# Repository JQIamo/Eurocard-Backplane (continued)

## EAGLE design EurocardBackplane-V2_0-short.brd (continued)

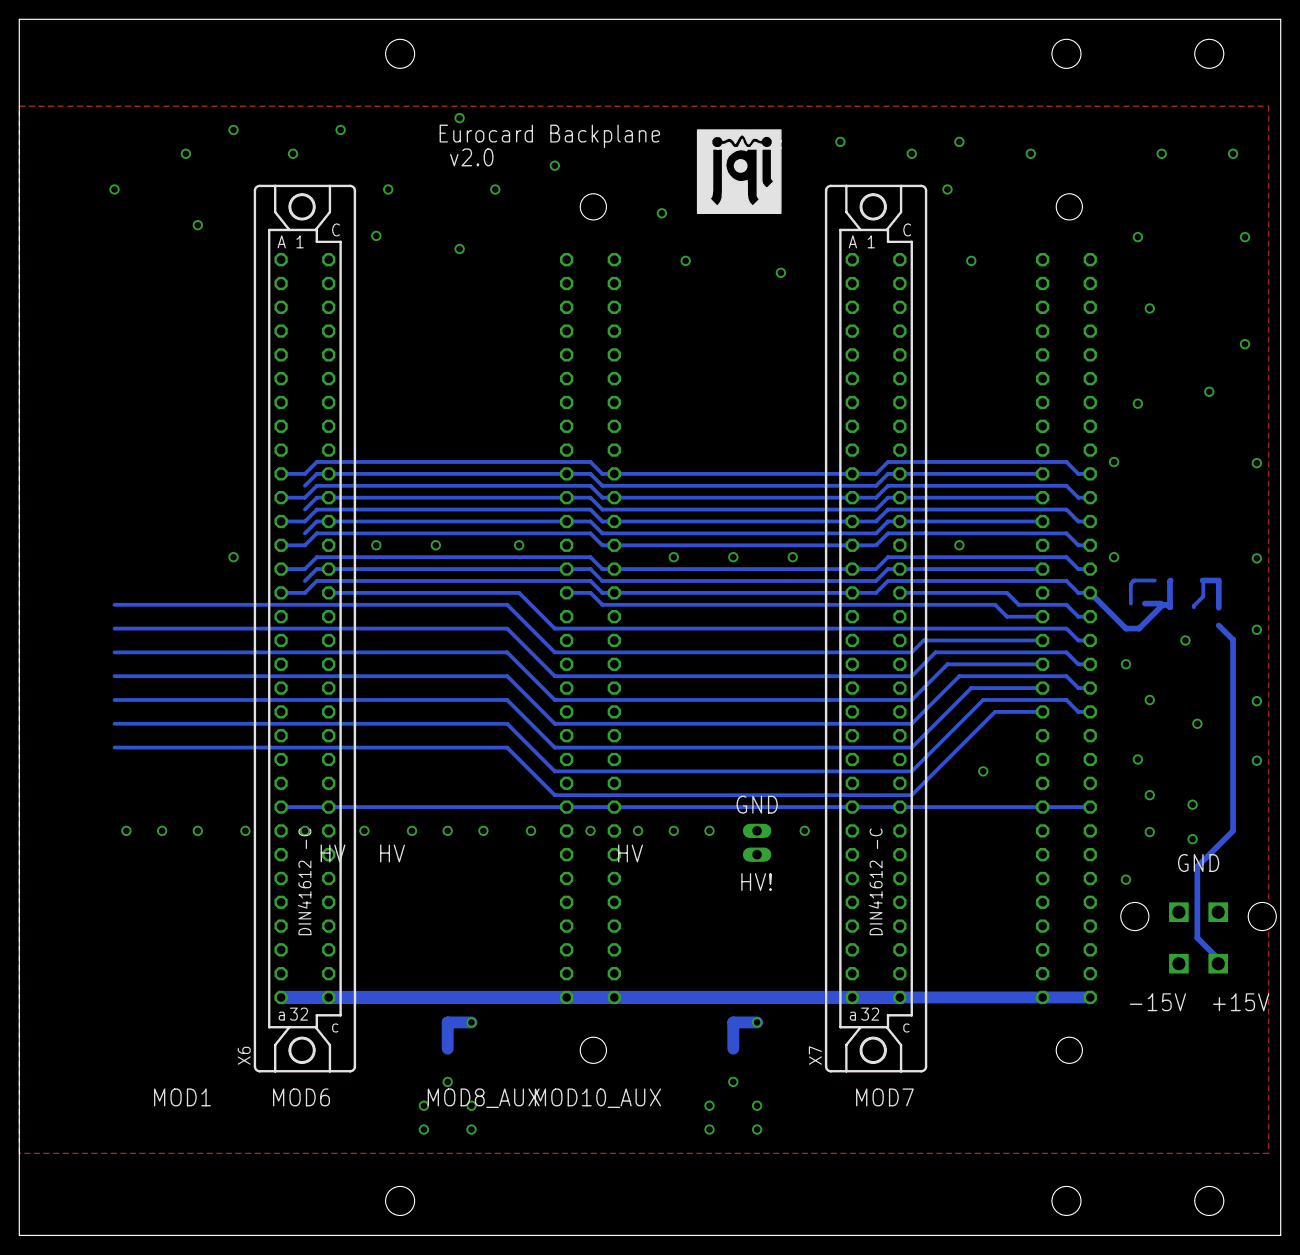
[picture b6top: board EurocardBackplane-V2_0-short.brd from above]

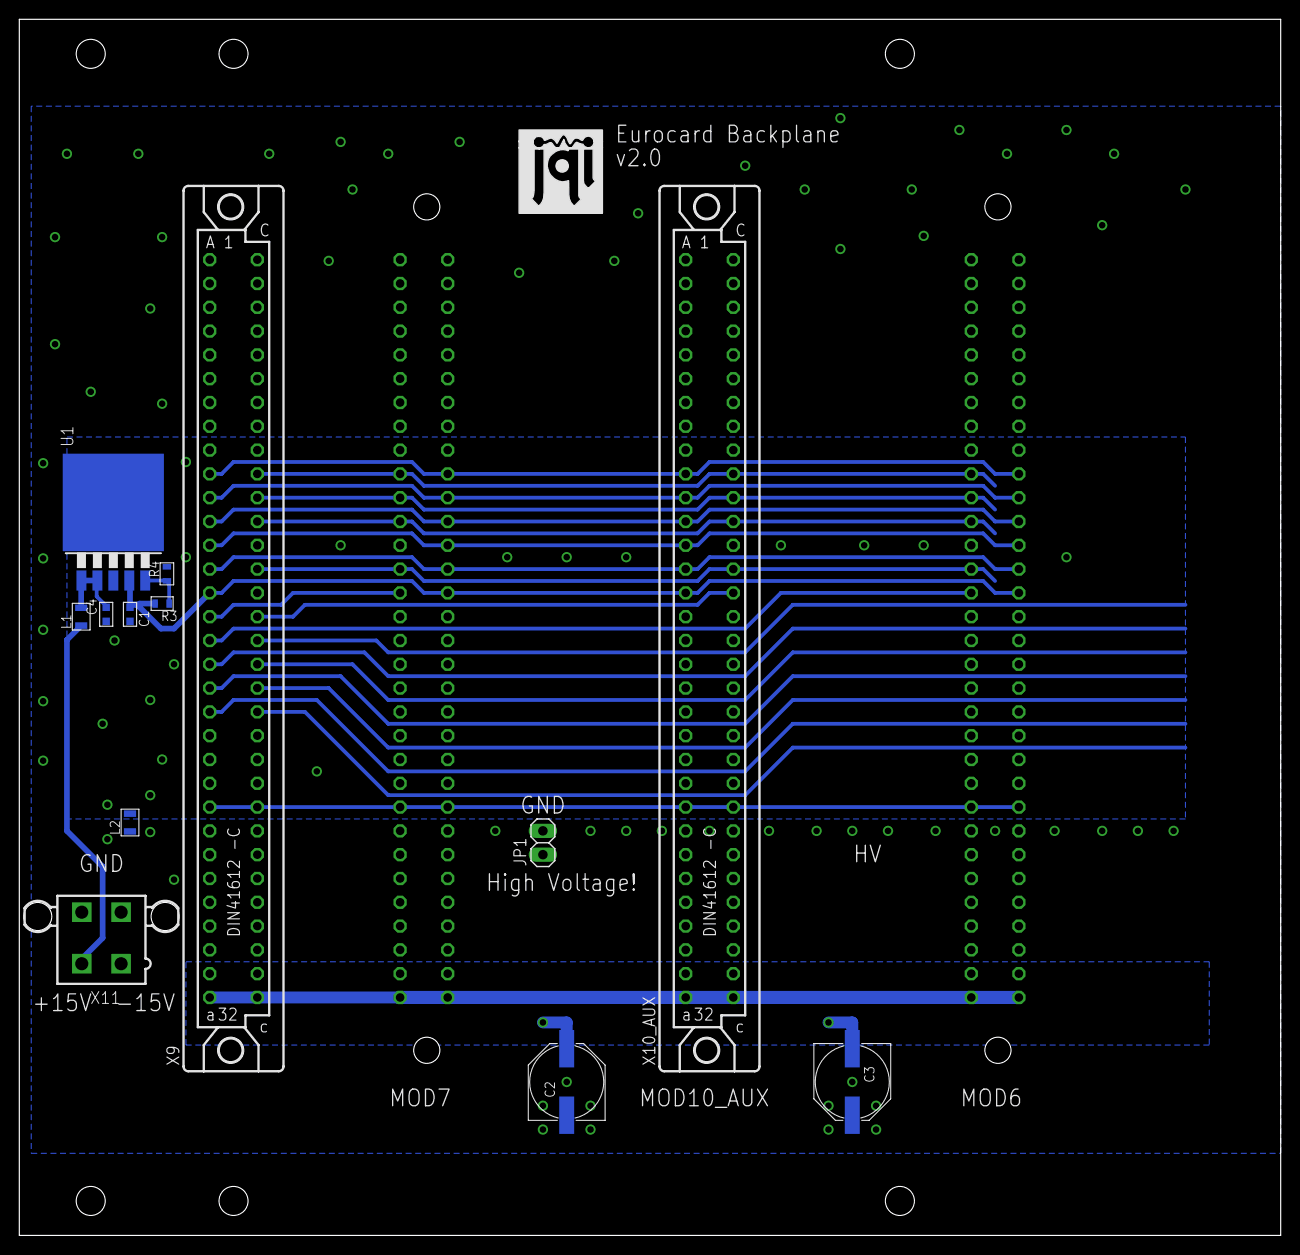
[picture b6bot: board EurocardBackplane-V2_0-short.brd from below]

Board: 4 copper layers, 134.6 x 129.8 mm, 18 parts (14 on the bottom side), 60 nets.

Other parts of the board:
U$1, U$4: JQI_LOGO_NEGATIVE-SILKSCREEN
U$2: BACKPLN-PROTO

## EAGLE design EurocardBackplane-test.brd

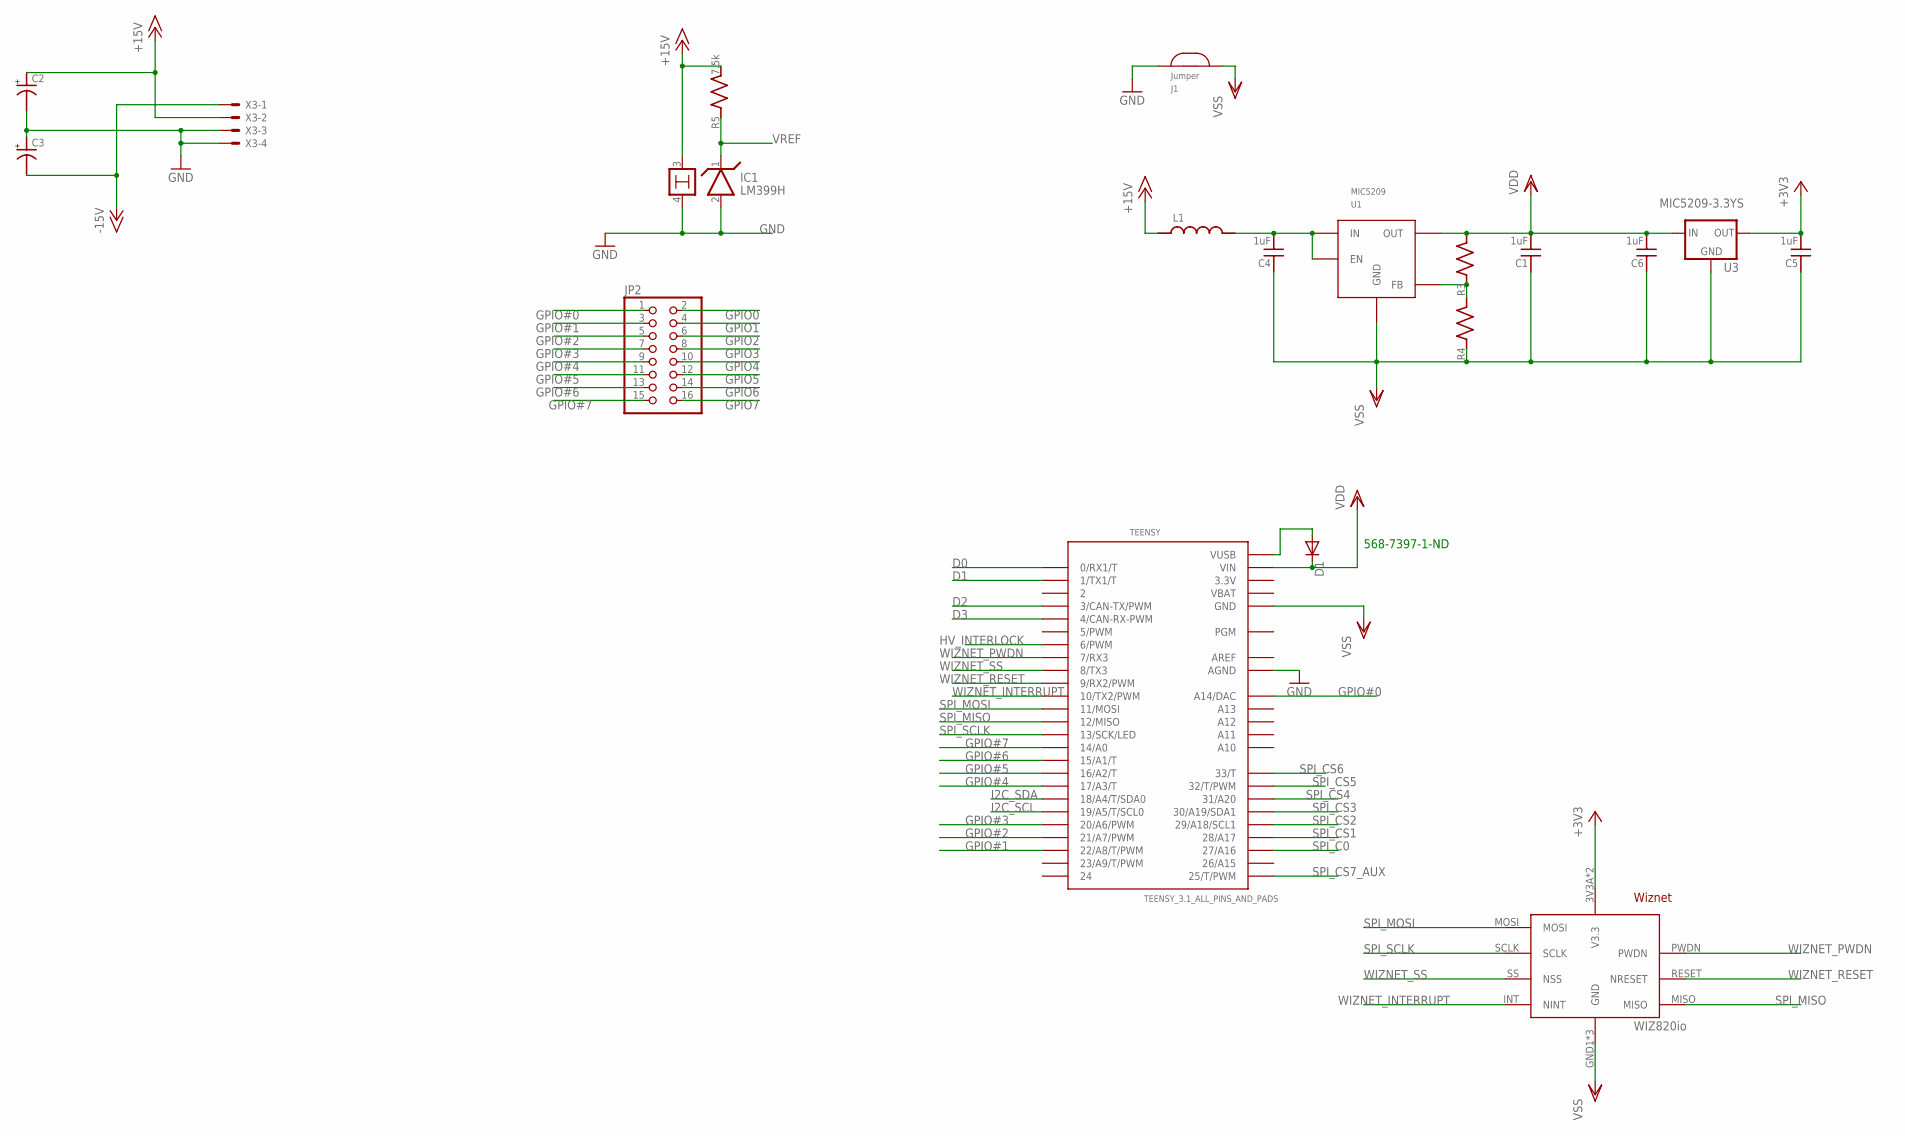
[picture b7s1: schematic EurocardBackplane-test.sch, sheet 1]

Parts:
C1, C4, C5, C6: 1uF; C_MLCC_0603
C2, C3: C_POL_SMDF; PANASONIC_F
D1: DIODE-SOD523; SOD523
IC1: LM399H; TO39/4
J1: JUMPER; JUMP
JP2: PINHD-2X8; 2X08
L1: L_FERRITE_SMDLFERRITE_0805; R_0805
R3, R4: R_SMDR0603; R_0603
R5: 7.5k; R_0603
TEENSY: TEENSY_3.1_ALL_PINS_AND_PADS; TEENSY_3.1_ALLPINS
U1: MIC5209; TO263-5
U2: WIZ820IO; WIZNET
U3: MIC5209-3.3YS; SOT223-S
X3: 5566-4

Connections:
3.3V: TEENSY.3.3V, TEENSY.3.3V1 (3.3V), TEENSY.3.3V2 (3.3V)
+3V3: C5.P$2 (2), U2.3V3A (V3.3), U2.3V3B (V3.3), U3.3 (OUT)
+15V: C2.+, IC1.3, L1.P$1 (1), R5.P$2 (2), X3.2; also elsewhere on the board
-15V: C3.-, X3.1; also elsewhere on the board
AREF: TEENSY.AREF
D0: TEENSY.0 (0/RX1/T); also elsewhere on the board
D1: TEENSY.1 (1/TX1/T); also elsewhere on the board
D2: TEENSY.3 (3/CAN-TX/PWM); also elsewhere on the board
D3: TEENSY.4 (4/CAN-RX-PWM); also elsewhere on the board
GND: C2.-, C3.+, IC1.2, IC1.4, J1.P$2, TEENSY.AGND, X3.3, X3.4; also elsewhere on the board
GPIO0: JP2.2; also elsewhere on the board
GPIO1: JP2.4; also elsewhere on the board
GPIO2: JP2.6; also elsewhere on the board
GPIO3: JP2.8; also elsewhere on the board
GPIO4: JP2.10; also elsewhere on the board
GPIO5: JP2.12; also elsewhere on the board
GPIO6: JP2.14; also elsewhere on the board
GPIO7: JP2.16; also elsewhere on the board
GPIO#0: JP2.1, TEENSY.A14 (A14/DAC)
GPIO#1: JP2.3, TEENSY.22/A8 (22/A8/T/PWM)
GPIO#2: JP2.5, TEENSY.21/A7 (21/A7/PWM)
GPIO#3: JP2.7, TEENSY.20/A6 (20/A6/PWM)
GPIO#4: JP2.9, TEENSY.17/A3 (17/A3/T)
GPIO#5: JP2.11, TEENSY.16/A2 (16/A2/T)
GPIO#6: JP2.13, TEENSY.15/A1 (15/A1/T)
GPIO#7: JP2.15, TEENSY.14/A0
HV_INTERLOCK: TEENSY.6 (6/PWM); also elsewhere on the board
I2C_SCL: TEENSY.19/A5 (19/A5/T/SCL0); also elsewhere on the board
I2C_SDA: TEENSY.18/A4 (18/A4/T/SDA0); also elsewhere on the board
unnamed: C4.P$2 (2), L1.P$2 (2), U1.1 (EN), U1.2 (IN)
unnamed: D1.A, TEENSY.VUSB
unnamed: R3.P$1 (1), R4.P$2 (2), U1.5 (FB)
SPI_C0: TEENSY.27 (27/A16)
SPI_CS1: TEENSY.28 (28/A17)
SPI_CS2: TEENSY.29 (29/A18/SCL1)
SPI_CS3: TEENSY.30 (30/A19/SDA1)
SPI_CS4: TEENSY.31 (31/A20)
SPI_CS5: TEENSY.32 (32/T/PWM); also elsewhere on the board
SPI_CS6: TEENSY.33 (33/T); also elsewhere on the board
SPI_CS7_AUX: TEENSY.25 (25/T/PWM); also elsewhere on the board
SPI_MISO: TEENSY.12 (12/MISO), U2.MISO; also elsewhere on the board
SPI_MOSI: TEENSY.11 (11/MOSI), U2.MOSI; also elsewhere on the board
SPI_SCLK: TEENSY.13 (13/SCK/LED), U2.SCLK; also elsewhere on the board
VBAT: TEENSY.VBAT
VDD: C1.P$2 (2), C6.P$2 (2), D1.C, R3.P$2 (2), TEENSY.VIN, U1.4 (OUT), U3.1 (IN)
VREF: IC1.1, R5.P$1 (1); also elsewhere on the board
VSS: C1.P$1 (1), C4.P$1 (1), C5.P$1 (1), C6.P$1 (1), J1.P$1, R4.P$1 (1), TEENSY.GND, TEENSY.GND1 (GND), TEENSY.GND2 (GND), U1.3 (GND), U1.6 (GND), U2.GND1 (GND), U2.GND2 (GND), U2.GND3 (GND), U3.2 (GND), U3.4 (GND)
WIZNET_INTERRUPT: TEENSY.10 (10/TX2/PWM), U2.INT (NINT)
WIZNET_PWDN: TEENSY.7 (7/RX3), U2.PWDN
WIZNET_RESET: TEENSY.9 (9/RX2/PWM), U2.RESET (NRESET)
WIZNET_SS: TEENSY.8 (8/TX3), U2.SS (NSS)

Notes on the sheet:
568-7397-1-ND

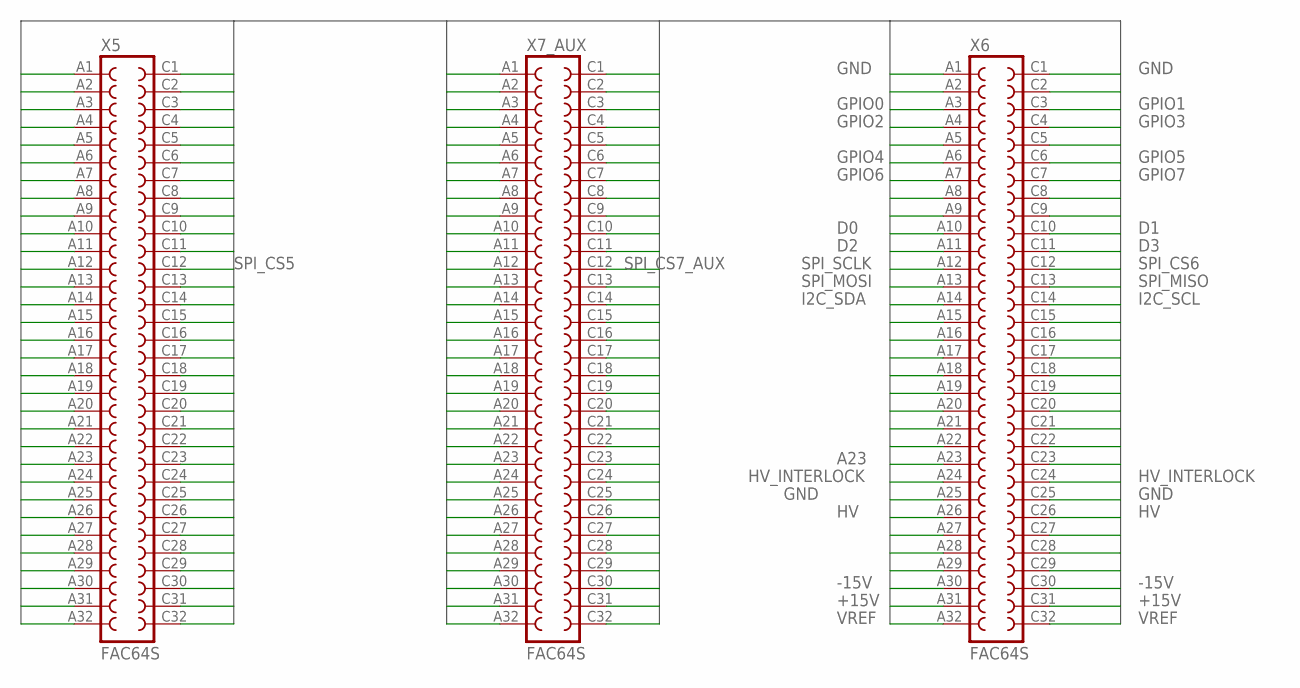
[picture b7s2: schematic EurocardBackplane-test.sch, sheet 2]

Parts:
X5, X6, X7_AUX: FAC64S

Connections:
+15V: X5.A31, X5.C31, X6.A31, X6.C31, X7_AUX.A31, X7_AUX.C31; also elsewhere on the board
-15V: X5.A30, X5.C30, X6.A30, X6.C30, X7_AUX.A30, X7_AUX.C30; also elsewhere on the board
A2: X5.A2, X6.A2, X7_AUX.A2
A5: X5.A5, X6.A5, X7_AUX.A5
A8: X5.A8, X6.A8, X7_AUX.A8
A9: X5.A9, X6.A9, X7_AUX.A9
A15: X5.A15, X6.A15, X7_AUX.A15
A16: X5.A16, X6.A16, X7_AUX.A16
A17: X5.A17, X6.A17, X7_AUX.A17
A18: X5.A18, X6.A18, X7_AUX.A18
A19: X5.A19, X6.A19, X7_AUX.A19
A20: X5.A20, X6.A20, X7_AUX.A20
A21: X5.A21, X6.A21, X7_AUX.A21
A22: X5.A22, X6.A22, X7_AUX.A22
A23: X5.A23, X6.A23, X7_AUX.A23
A27: X5.A27, X6.A27, X7_AUX.A27
A28: X5.A28, X6.A28, X7_AUX.A28
A29: X5.A29, X6.A29, X7_AUX.A29
C2: X5.C2, X6.C2, X7_AUX.C2
C5: X5.C5, X6.C5, X7_AUX.C5
C8: X5.C8, X6.C8, X7_AUX.C8
C9: X5.C9, X6.C9, X7_AUX.C9
C15: X5.C15, X6.C15, X7_AUX.C15
C16: X5.C16, X6.C16, X7_AUX.C16
C17: X5.C17, X6.C17, X7_AUX.C17
C18: X5.C18, X6.C18, X7_AUX.C18
C19: X5.C19, X6.C19, X7_AUX.C19
C20: X5.C20, X6.C20, X7_AUX.C20
C21: X5.C21, X6.C21, X7_AUX.C21
C22: X5.C22, X6.C22, X7_AUX.C22
C23: X5.C23, X6.C23, X7_AUX.C23
C27: X5.C27, X6.C27, X7_AUX.C27
C28: X5.C28, X6.C28, X7_AUX.C28
C29: X5.C29, X6.C29, X7_AUX.C29
D0: X5.A10, X6.A10, X7_AUX.A10; also elsewhere on the board
D1: X5.C10, X6.C10, X7_AUX.C10; also elsewhere on the board
D2: X5.A11, X6.A11, X7_AUX.A11; also elsewhere on the board
D3: X5.C11, X6.C11, X7_AUX.C11; also elsewhere on the board
GND: X5.A1, X5.A25, X5.C1, X5.C25, X6.A1, X6.A25, X6.C1, X6.C25, X7_AUX.A1, X7_AUX.A25, X7_AUX.C1, X7_AUX.C25; also elsewhere on the board
GPIO0: X5.A3, X6.A3, X7_AUX.A3; also elsewhere on the board
GPIO1: X5.C3, X6.C3, X7_AUX.C3; also elsewhere on the board
GPIO2: X5.A4, X6.A4, X7_AUX.A4; also elsewhere on the board
GPIO3: X5.C4, X6.C4, X7_AUX.C4; also elsewhere on the board
GPIO4: X5.A6, X6.A6, X7_AUX.A6; also elsewhere on the board
GPIO5: X5.C6, X6.C6, X7_AUX.C6; also elsewhere on the board
GPIO6: X5.A7, X6.A7, X7_AUX.A7; also elsewhere on the board
GPIO7: X5.C7, X6.C7, X7_AUX.C7; also elsewhere on the board
HV: X5.A26, X5.C26, X6.A26, X6.C26, X7_AUX.A26, X7_AUX.C26
HV_INTERLOCK: X5.A24, X5.C24, X6.A24, X6.C24, X7_AUX.A24, X7_AUX.C24; also elsewhere on the board
I2C_SCL: X5.C14, X6.C14, X7_AUX.C14; also elsewhere on the board
I2C_SDA: X5.A14, X6.A14, X7_AUX.A14; also elsewhere on the board
SPI_CS5: X5.C12; also elsewhere on the board
SPI_CS6: X6.C12; also elsewhere on the board
SPI_CS7_AUX: X7_AUX.C12; also elsewhere on the board
SPI_MISO: X5.C13, X6.C13, X7_AUX.C13; also elsewhere on the board
SPI_MOSI: X5.A13, X6.A13, X7_AUX.A13; also elsewhere on the board
SPI_SCLK: X5.A12, X6.A12, X7_AUX.A12; also elsewhere on the board
VREF: X5.A32, X5.C32, X6.A32, X6.C32, X7_AUX.A32, X7_AUX.C32; also elsewhere on the board

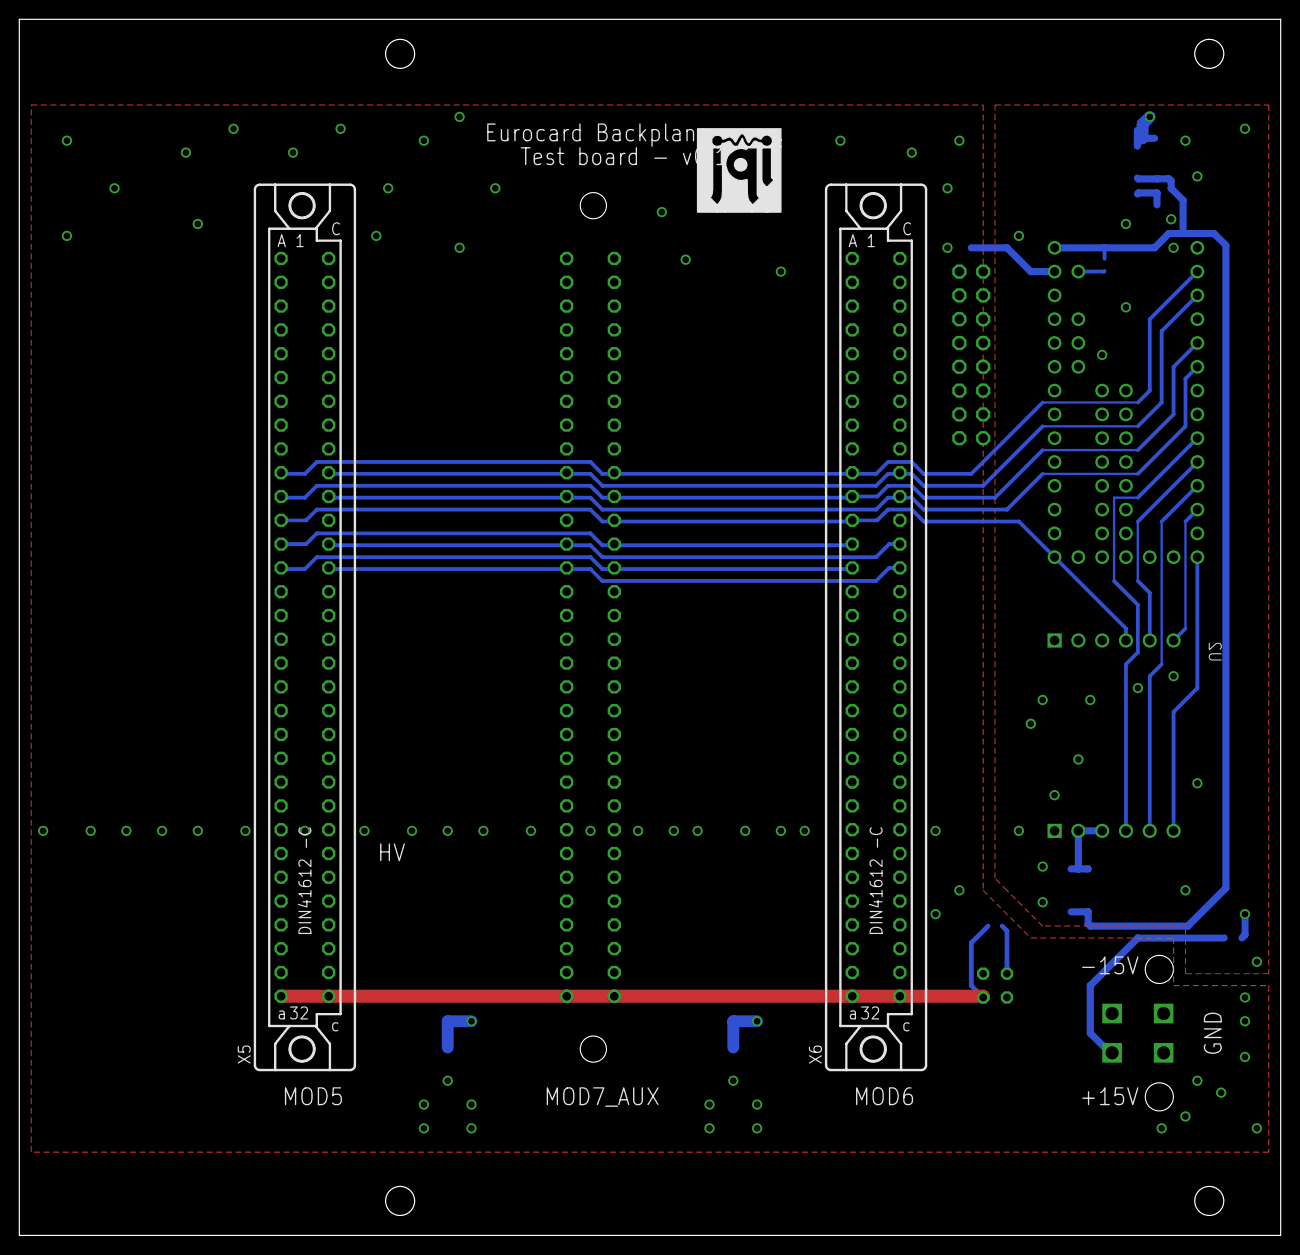
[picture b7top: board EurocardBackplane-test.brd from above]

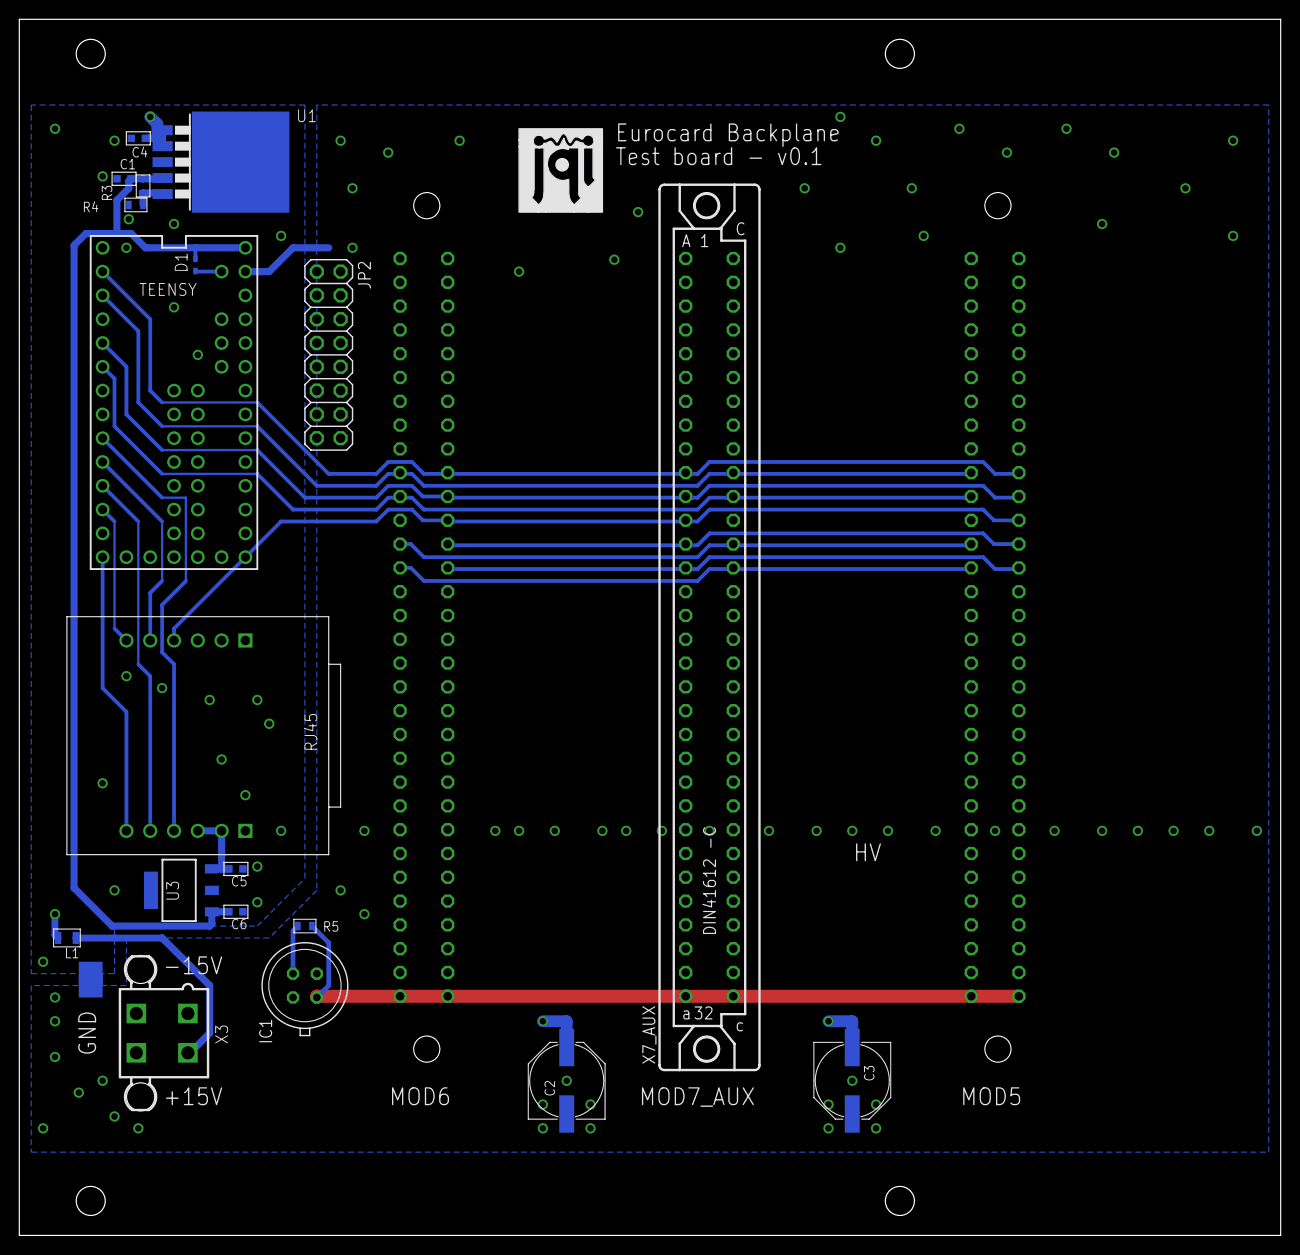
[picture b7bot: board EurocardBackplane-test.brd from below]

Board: 4 copper layers, 134.6 x 129.8 mm, 25 parts (21 on the bottom side), 77 nets.

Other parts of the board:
U$1, U$4: JQI_LOGO_NEGATIVE-SILKSCREEN
U$3: BACKPLN-PROTO

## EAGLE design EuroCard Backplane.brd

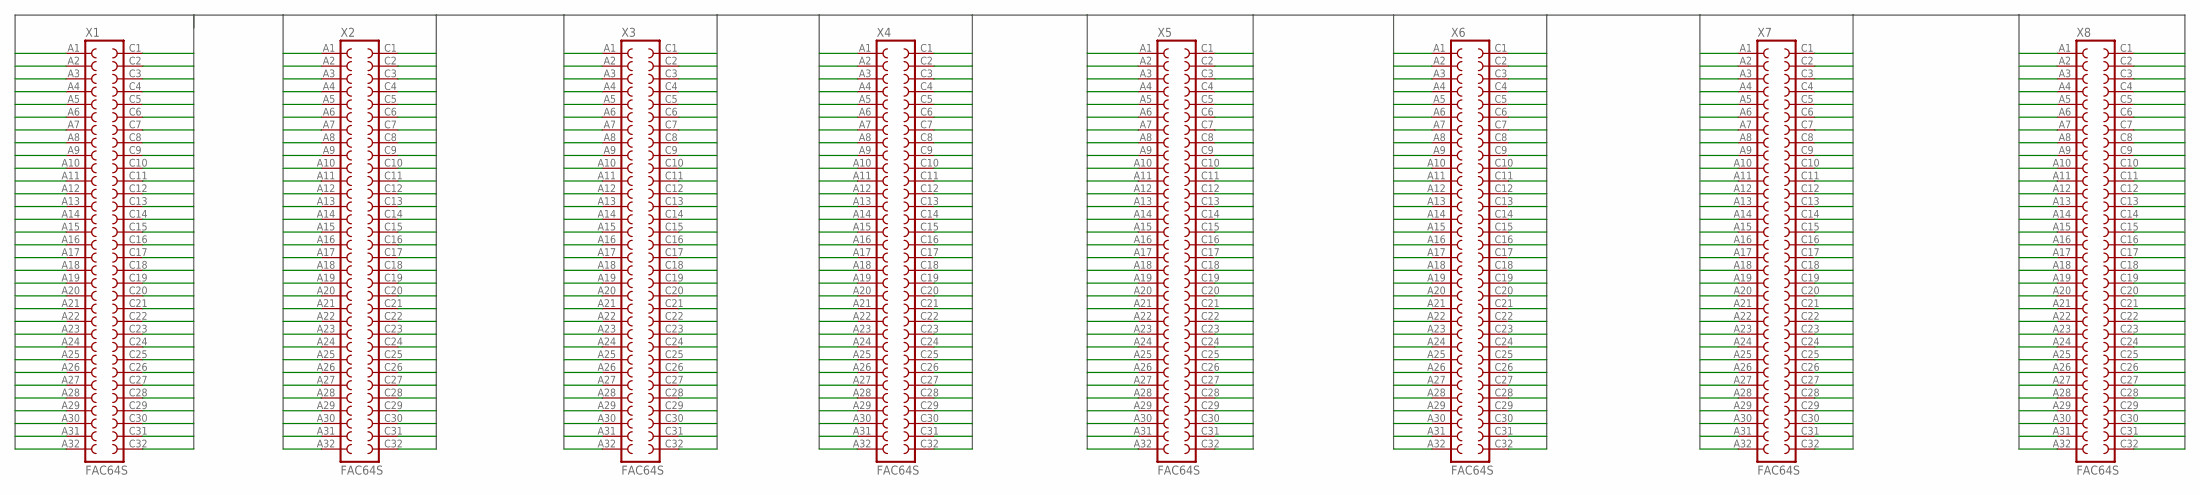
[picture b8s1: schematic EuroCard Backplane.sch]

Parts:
X1, X2, X3, X4, X5, X6, X7, X8: FAC64S

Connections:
A1: X1.A1, X2.A1, X3.A1, X4.A1, X5.A1, X6.A1, X7.A1, X8.A1
A2: X1.A2, X2.A2, X3.A2, X4.A2, X5.A2, X6.A2, X7.A2, X8.A2
A3: X1.A3, X2.A3, X3.A3, X4.A3, X5.A3, X6.A3, X7.A3, X8.A3
A4: X1.A4, X2.A4, X3.A4, X4.A4, X5.A4, X6.A4, X7.A4, X8.A4
A5: X1.A5, X2.A5, X3.A5, X4.A5, X5.A5, X6.A5, X7.A5, X8.A5
A6: X1.A6, X2.A6, X3.A6, X4.A6, X5.A6, X6.A6, X7.A6, X8.A6
A7: X1.A7, X2.A7, X3.A7, X4.A7, X5.A7, X6.A7, X7.A7, X8.A7
A8: X1.A8, X2.A8, X3.A8, X4.A8, X5.A8, X6.A8, X7.A8, X8.A8
A9: X1.A9, X2.A9, X3.A9, X4.A9, X5.A9, X6.A9, X7.A9, X8.A9
A10: X1.A10, X2.A10, X3.A10, X4.A10, X5.A10, X6.A10, X7.A10, X8.A10
A11: X1.A11, X2.A11, X3.A11, X4.A11, X5.A11, X6.A11, X7.A11, X8.A11
A12: X1.A12, X2.A12, X3.A12, X4.A12, X5.A12, X6.A12, X7.A12, X8.A12
A13: X1.A13, X2.A13, X3.A13, X4.A13, X5.A13, X6.A13, X7.A13, X8.A13
A14: X1.A14, X2.A14, X3.A14, X4.A14, X5.A14, X6.A14, X7.A14, X8.A14
A15: X1.A15, X2.A15, X3.A15, X4.A15, X5.A15, X6.A15, X7.A15, X8.A15
A16: X1.A16, X2.A16, X3.A16, X4.A16, X5.A16, X6.A16, X7.A16, X8.A16
A17: X1.A17, X2.A17, X3.A17, X4.A17, X5.A17, X6.A17, X7.A17, X8.A17
A18: X1.A18, X2.A18, X3.A18, X4.A18, X5.A18, X6.A18, X7.A18, X8.A18
A19: X1.A19, X2.A19, X3.A19, X4.A19, X5.A19, X6.A19, X7.A19, X8.A19
A20: X1.A20, X2.A20, X3.A20, X4.A20, X5.A20, X6.A20, X7.A20, X8.A20
A21: X1.A21, X2.A21, X3.A21, X4.A21, X5.A21, X6.A21, X7.A21, X8.A21
A22: X1.A22, X2.A22, X3.A22, X4.A22, X5.A22, X6.A22, X7.A22, X8.A22
A23: X1.A23, X2.A23, X3.A23, X4.A23, X5.A23, X6.A23, X7.A23, X8.A23
A24: X1.A24, X2.A24, X3.A24, X4.A24, X5.A24, X6.A24, X7.A24, X8.A24
A25: X1.A25, X2.A25, X3.A25, X4.A25, X5.A25, X6.A25, X7.A25, X8.A25
A26: X1.A26, X2.A26, X3.A26, X4.A26, X5.A26, X6.A26, X7.A26, X8.A26
A27: X1.A27, X2.A27, X3.A27, X4.A27, X5.A27, X6.A27, X7.A27, X8.A27
A28: X1.A28, X2.A28, X3.A28, X4.A28, X5.A28, X6.A28, X7.A28, X8.A28
A29: X1.A29, X2.A29, X3.A29, X4.A29, X5.A29, X6.A29, X7.A29, X8.A29
A30: X1.A30, X2.A30, X3.A30, X4.A30, X5.A30, X6.A30, X7.A30, X8.A30
A31: X1.A31, X2.A31, X3.A31, X4.A31, X5.A31, X6.A31, X7.A31, X8.A31
A32: X1.A32, X2.A32, X3.A32, X4.A32, X5.A32, X6.A32, X7.A32, X8.A32
C1: X1.C1, X2.C1, X3.C1, X4.C1, X5.C1, X6.C1, X7.C1, X8.C1
C2: X1.C2, X2.C2, X3.C2, X4.C2, X5.C2, X6.C2, X7.C2, X8.C2
C3: X1.C3, X2.C3, X3.C3, X4.C3, X5.C3, X6.C3, X7.C3, X8.C3
C4: X1.C4, X2.C4, X3.C4, X4.C4, X5.C4, X6.C4, X7.C4, X8.C4
C5: X1.C5, X2.C5, X3.C5, X4.C5, X5.C5, X6.C5, X7.C5, X8.C5
C6: X1.C6, X2.C6, X3.C6, X4.C6, X5.C6, X6.C6, X7.C6, X8.C6
C7: X1.C7, X2.C7, X3.C7, X4.C7, X5.C7, X6.C7, X7.C7, X8.C7
C8: X1.C8, X2.C8, X3.C8, X4.C8, X5.C8, X6.C8, X7.C8, X8.C8
C9: X1.C9, X2.C9, X3.C9, X4.C9, X5.C9, X6.C9, X7.C9, X8.C9
C10: X1.C10, X2.C10, X3.C10, X4.C10, X5.C10, X6.C10, X7.C10, X8.C10
C11: X1.C11, X2.C11, X3.C11, X4.C11, X5.C11, X6.C11, X7.C11, X8.C11
C12: X1.C12, X2.C12, X3.C12, X4.C12, X5.C12, X6.C12, X7.C12, X8.C12
C13: X1.C13, X2.C13, X3.C13, X4.C13, X5.C13, X6.C13, X7.C13, X8.C13
C14: X1.C14, X2.C14, X3.C14, X4.C14, X5.C14, X6.C14, X7.C14, X8.C14
C15: X1.C15, X2.C15, X3.C15, X4.C15, X5.C15, X6.C15, X7.C15, X8.C15
C16: X1.C16, X2.C16, X3.C16, X4.C16, X5.C16, X6.C16, X7.C16, X8.C16
C17: X1.C17, X2.C17, X3.C17, X4.C17, X5.C17, X6.C17, X7.C17, X8.C17
C18: X1.C18, X2.C18, X3.C18, X4.C18, X5.C18, X6.C18, X7.C18, X8.C18
C19: X1.C19, X2.C19, X3.C19, X4.C19, X5.C19, X6.C19, X7.C19, X8.C19
C20: X1.C20, X2.C20, X3.C20, X4.C20, X5.C20, X6.C20, X7.C20, X8.C20
C21: X1.C21, X2.C21, X3.C21, X4.C21, X5.C21, X6.C21, X7.C21, X8.C21
C22: X1.C22, X2.C22, X3.C22, X4.C22, X5.C22, X6.C22, X7.C22, X8.C22
C23: X1.C23, X2.C23, X3.C23, X4.C23, X5.C23, X6.C23, X7.C23, X8.C23
C24: X1.C24, X2.C24, X3.C24, X4.C24, X5.C24, X6.C24, X7.C24, X8.C24
C25: X1.C25, X2.C25, X3.C25, X4.C25, X5.C25, X6.C25, X7.C25, X8.C25
C26: X1.C26, X2.C26, X3.C26, X4.C26, X5.C26, X6.C26, X7.C26, X8.C26
C27: X1.C27, X2.C27, X3.C27, X4.C27, X5.C27, X6.C27, X7.C27, X8.C27
C28: X1.C28, X2.C28, X3.C28, X4.C28, X5.C28, X6.C28, X7.C28, X8.C28
C29: X1.C29, X2.C29, X3.C29, X4.C29, X5.C29, X6.C29, X7.C29, X8.C29
C30: X1.C30, X2.C30, X3.C30, X4.C30, X5.C30, X6.C30, X7.C30, X8.C30
C31: X1.C31, X2.C31, X3.C31, X4.C31, X5.C31, X6.C31, X7.C31, X8.C31
C32: X1.C32, X2.C32, X3.C32, X4.C32, X5.C32, X6.C32, X7.C32, X8.C32

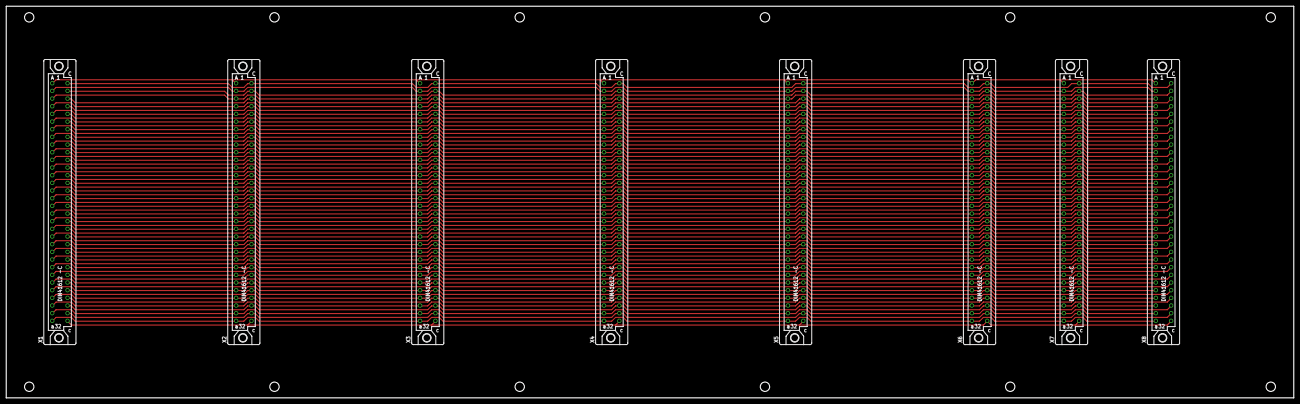
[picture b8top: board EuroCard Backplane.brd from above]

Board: 4 copper layers, 426.7 x 129.8 mm, 9 parts (0 on the bottom side), 64 nets.

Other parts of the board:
U$1: BACKPLANE

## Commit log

2015-03-16 Started repository
    Files so far consist of 8 connectors and mechanical mounting holes
2015-03-16 Updated gitignore to include .pro autorouting files
2015-03-22 Added eagle .epf project file and description
2015-03-22 Added starter schematic for Eurocard modules
2015-04-16 Add a couple dimensions to board
2015-04-16 Stub for test backplane
2015-04-17 Mostly-routed test board with teensy, WIZNET, and vref.
2015-04-19 routing and layout of test board done
2015-04-19 Added Gerber files for eurocard-backplane-test
2015-10-13 updated test backplane
2015-10-13 Started V1.0
2015-10-14 Halfway done adding more connectors
2015-10-16 Incremental progress
2015-10-19 Version 1.0 board layout pretty much done
2015-11-17 Started Version 2: Better digital line shielding, microcontroller moved off board
2015-11-19 Added note to include QR code on silkscreen for production run
2015-11-19 Made short version of backplane for digital noise testing
2015-11-20 added .zip to gitignore
2016-01-30 Unsure what these changes are; stashing them here.
    Might be able to just delete this branch later.
2016-01-30 Stub schematic for MCU backplane board
    Really just for noise testing at this point; should be modified when
    we're ready to make the final deal.
2018-01-30 stashed progress to share
2018-01-30 cleaned up directory
2018-07-19 adding just few traces
2018-08-02 Confused about L2 inductor and 5V supply for the TBX0108
